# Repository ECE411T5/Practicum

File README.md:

# Practicum
Portland State University. Electrical and Computer Engineering Department. ECE 411 Practicum Project

## Team 5
* jdhobby       - Joshua Hobby
* CompileMyLife - Ibrahim Binmahfood
* Ghonimo       - Mohamed Ghonim
* DrFumador     - Mohamed Ashkanani

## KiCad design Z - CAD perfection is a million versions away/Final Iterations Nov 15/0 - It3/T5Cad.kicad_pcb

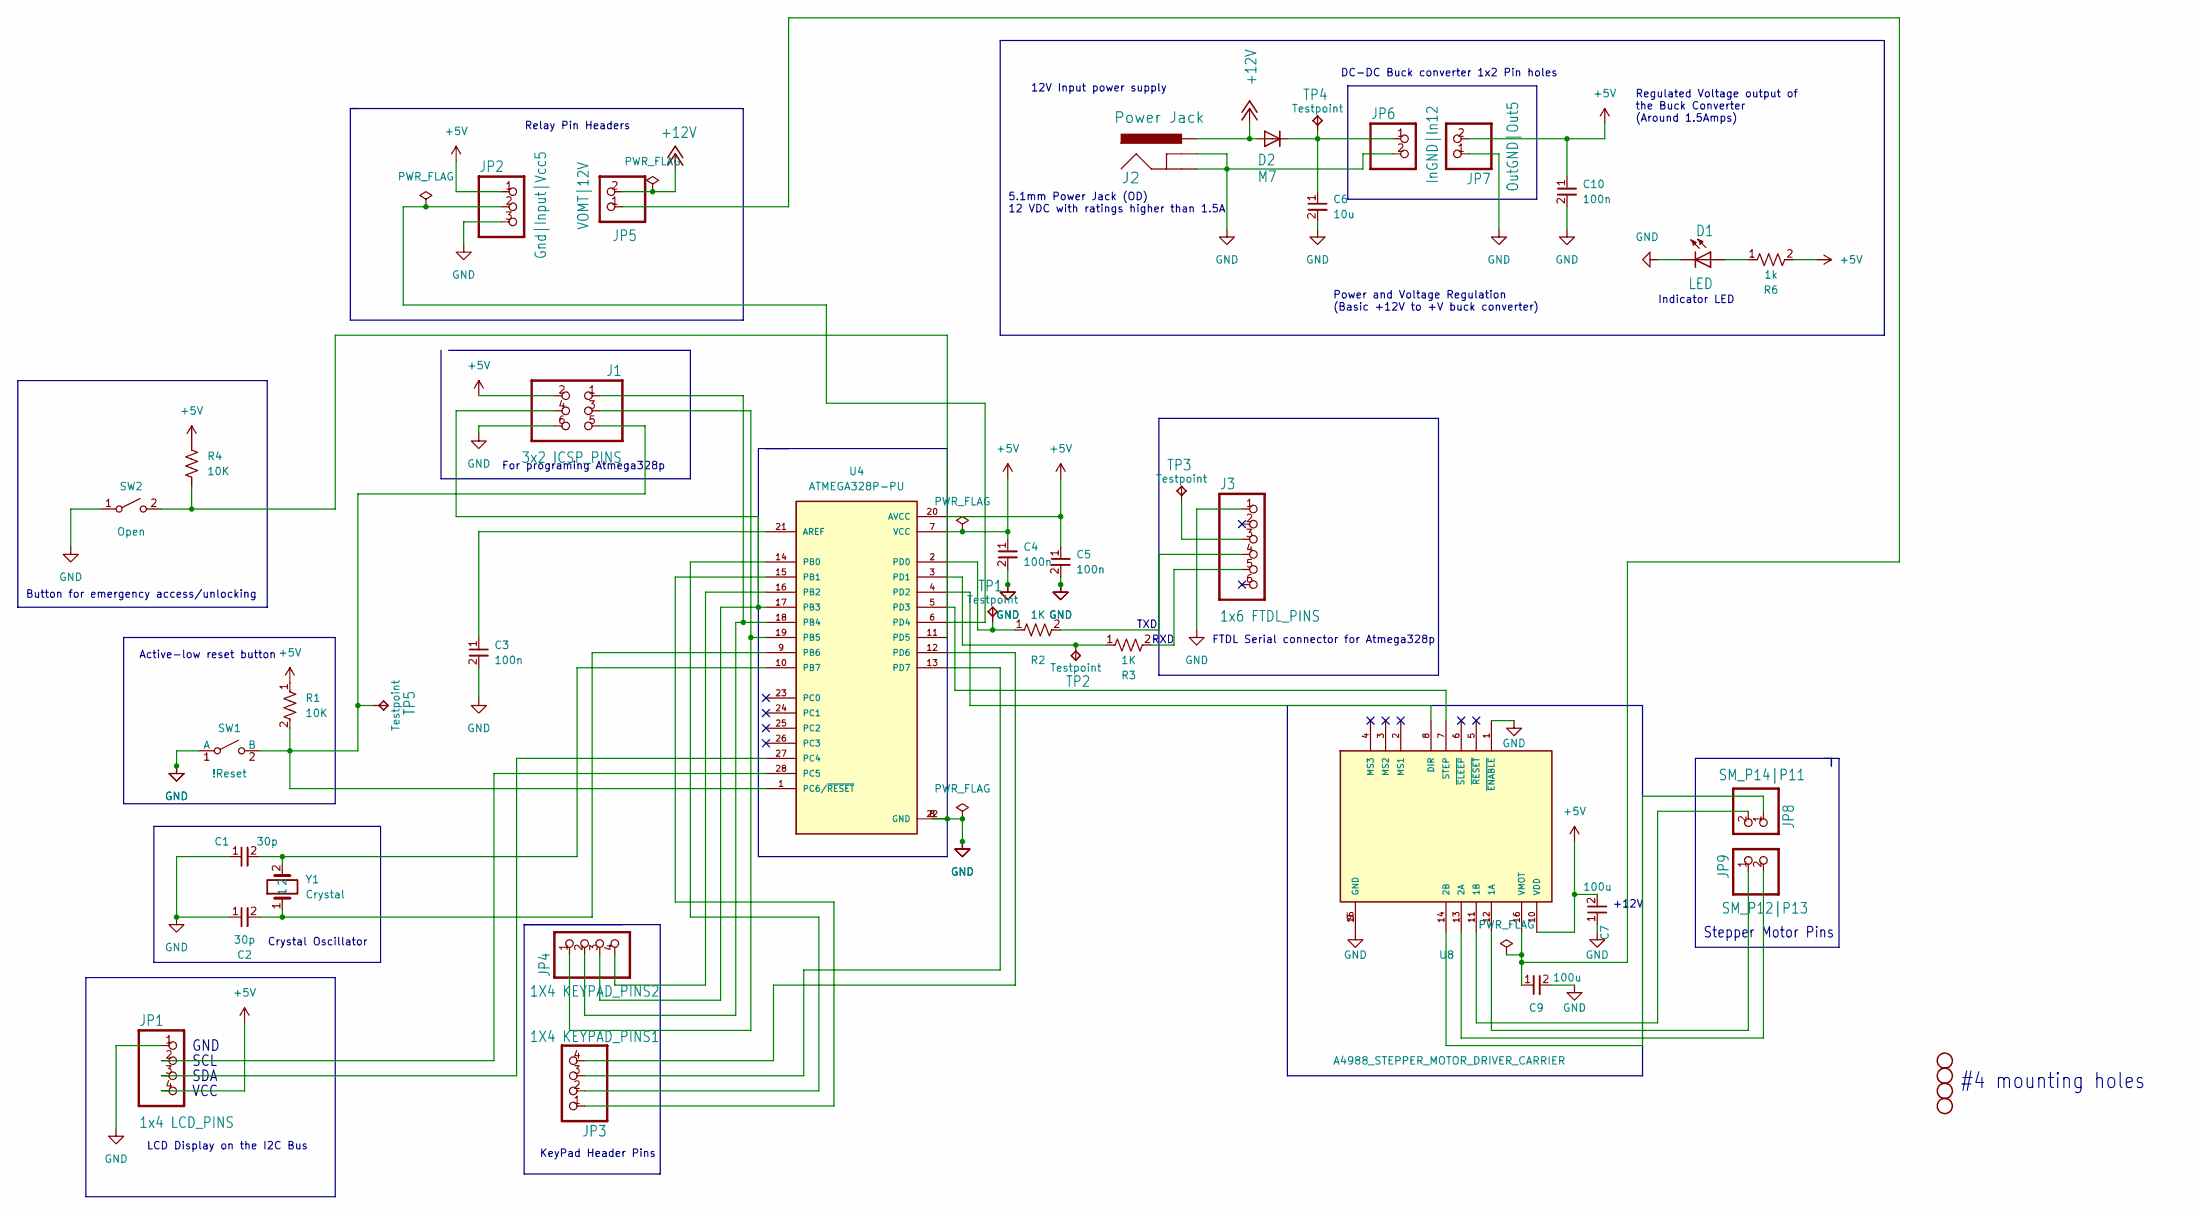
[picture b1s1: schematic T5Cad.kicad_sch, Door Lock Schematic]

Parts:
C1, C2: 30p; C0805K
C3, C4, C5, C10: 100n; C0805K
C6: 10u; C0805K
C7, C9: 100u; C0805K
D1: CHIP-LED0805
D2: SMB
H1, H2, H3, H4: STAND-OFF
J1: 2X03
J2: POWER_JACK_PTH
J3: 1X06
JP1: 1x4 LCD_PINS; 1X04
JP2: Gnd|Input|Vcc5; 1X03
JP3: 1X4 KEYPAD_PINS1; 1X04
JP4: 1X4 KEYPAD_PINS2; 1X04
JP5: VOMT|12V; 1X02
JP6: InGND|In12; 1X02
JP7: OutGND|Out5; 1X02
JP8: SM_P14|P11; 1X02
JP9: SM_P12|P13; 1X02
R1, R4: 10K; R0805
R2, R3: 1K; R0805
R6: 1k; R0805
SW1: !Reset; TACTILE_SWITCH_SMD
SW2: Open; TACTILE_SWITCH_SMD
TP1, TP2, TP3, TP4, TP5: Testpoint; P1-13
U4: ATMEGA328P-PU; DIL28-3
U8: A4988_STEPPER_MOTOR_DRIVER_CARRIER; MODULE_A4988_STEPPER_MOTOR_DRIVER_CARRIER
Y1: Crystal; HC49UP

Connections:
+5V: C4.1, C5.1, C7.2, C10.1, J1.2, JP1.4, JP2.1, JP7.2, R1.1, R4.1, R6.2, U4.7 (VCC), U4.20 (AVCC), U8.10 (VDD)
+12V: D2.A, J2.PWR, JP5.2
GND: C1.1, C2.1, C3.2, C4.2, C5.2, C6.2, C7.1, C9.2, C10.2, D1.C, J1.6, J2.GND, J2.GNDBREAK, J3.1, JP1.1, JP2.3, JP6.2, JP7.1, SW1.1 (A), SW2.1 (A), U4.8 (GND), U4.22 (GND), U8.1 (~ENABLE), U8.9 (GND), U8.15 (GND)
unnamed: C1.2, U4.10 (PB7), Y1.2
unnamed: C2.2, U4.9 (PB6), Y1.1
unnamed: C3.1, U4.21 (AREF)
unnamed: C6.1, D2.C, JP6.1, TP4.TP
unnamed: C9.1, JP5.1, U8.16 (VMOT)
unnamed: D1.A, R6.1
unnamed: J1.1, JP4.2, U4.18 (PB4)
unnamed: J1.3, JP4.1, U4.19 (PB5)
unnamed: J1.4, JP4.3, U4.17 (PB3)
unnamed: J1.5, R1.2, SW1.2 (B), TP5.TP, U4.1 (PC6/~RESET)
unnamed: J3.3, TP3.TP
unnamed: J3.4, R2.2
unnamed: J3.5, R3.2
unnamed: JP1.2, U4.28 (PC5)
unnamed: JP1.3, U4.27 (PC4)
unnamed: JP2.2, U4.6 (PD4)
unnamed: JP3.1, U4.15 (PB1)
unnamed: JP3.2, U4.14 (PB0)
unnamed: JP3.3, U4.13 (PD7)
unnamed: JP3.4, U4.12 (PD6)
unnamed: JP4.4, U4.16 (PB2)
unnamed: JP8.1, U8.14 (2B)
unnamed: JP8.2, U8.11 (1B)
unnamed: JP9.1, U8.12 (1A)
unnamed: JP9.2, U8.13 (2A)
unnamed: R2.1, TP1.TP, U4.2 (PD0)
unnamed: R3.1, TP2.TP, U4.3 (PD1)
unnamed: R4.2, SW2.2 (B), U4.11 (PD5)
unnamed: U4.4 (PD2), U8.8 (DIR)
unnamed: U4.5 (PD3), U8.7 (STEP)

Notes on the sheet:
SCL
#4 mounting holes
12V Input power supply
DC-DC Buck converter 1x2 Pin holes
KeyPad Header Pins
FTDL Serial connector for Atmega328p
Relay Pin Headers
LCD Display on the I2C Bus
RXD
Power and Voltage Regulation (Basic +12V to +V buck converter)
Button for emergency access/unlocking
Stepper Motor Pins
For programing Atmega328p
5.1mm Power Jack (OD) 12 VDC with ratings higher than 1.5A
Active-low reset button
+12V
VCC
Regulated Voltage output of the Buck Converter (Around 1.5Amps)
TXD
Indicator LED
GND
SDA
Crystal Oscillator

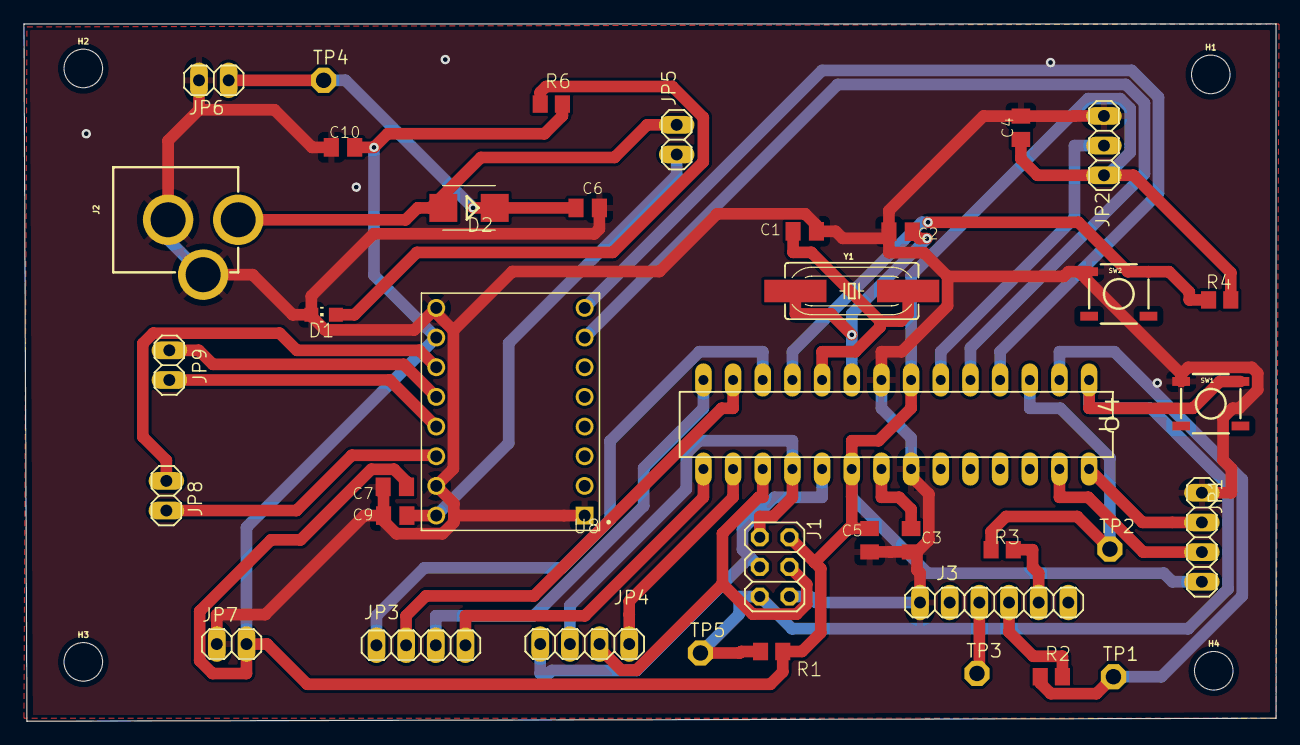
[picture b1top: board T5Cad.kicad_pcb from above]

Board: 2 copper layers, 107.2 x 59.7 mm, 42 parts (0 on the bottom side), 33 nets.

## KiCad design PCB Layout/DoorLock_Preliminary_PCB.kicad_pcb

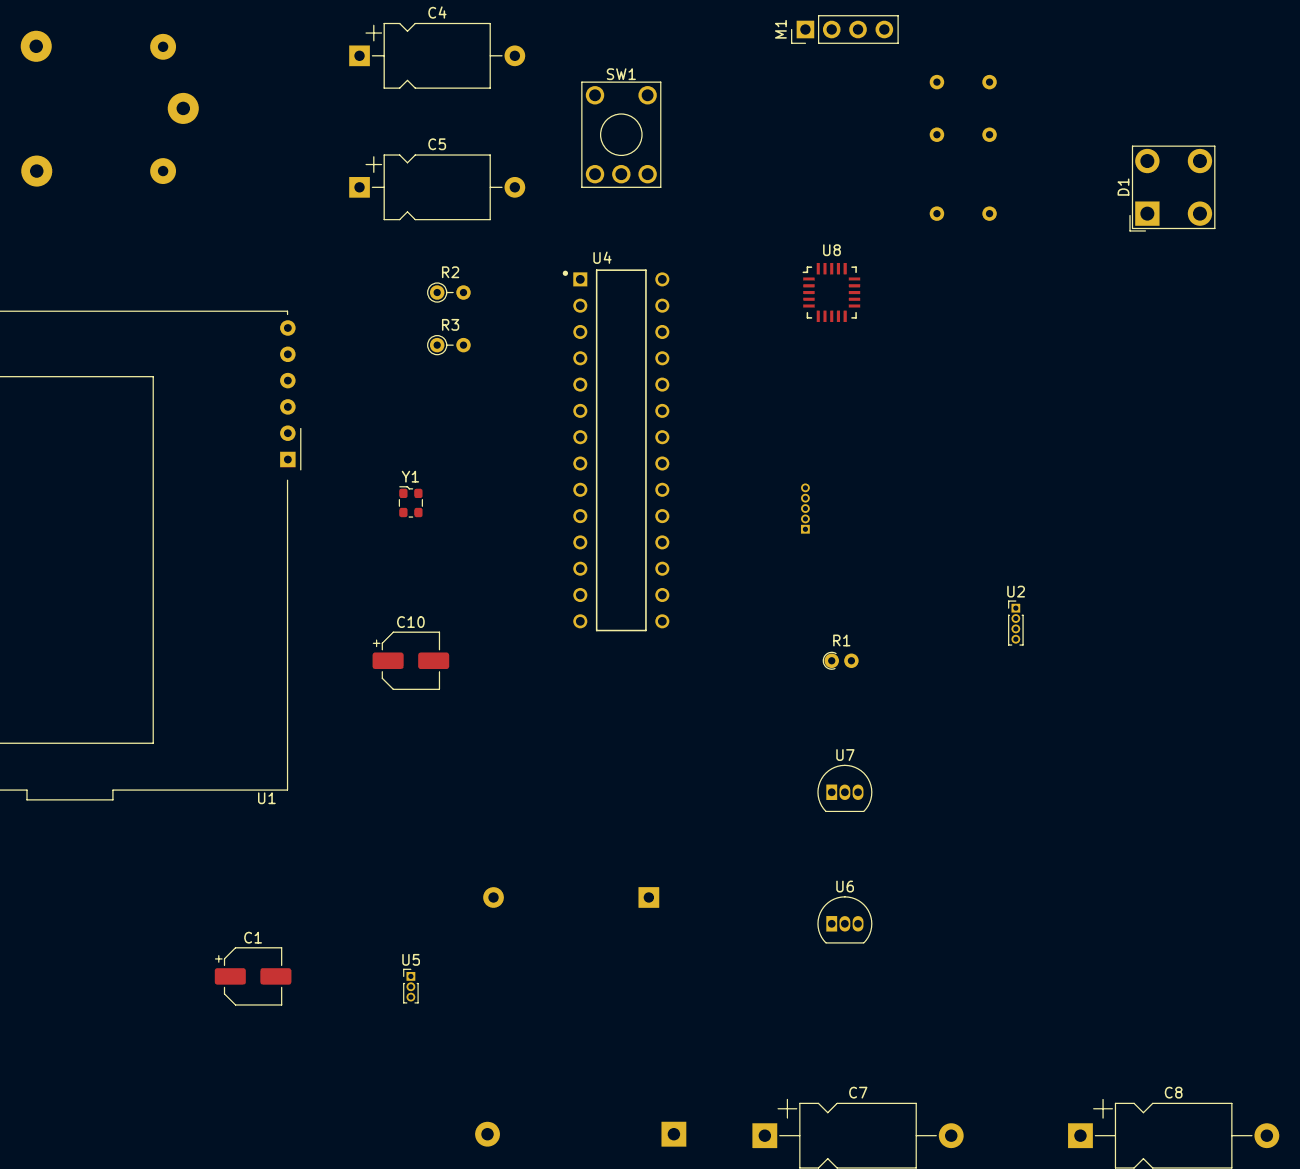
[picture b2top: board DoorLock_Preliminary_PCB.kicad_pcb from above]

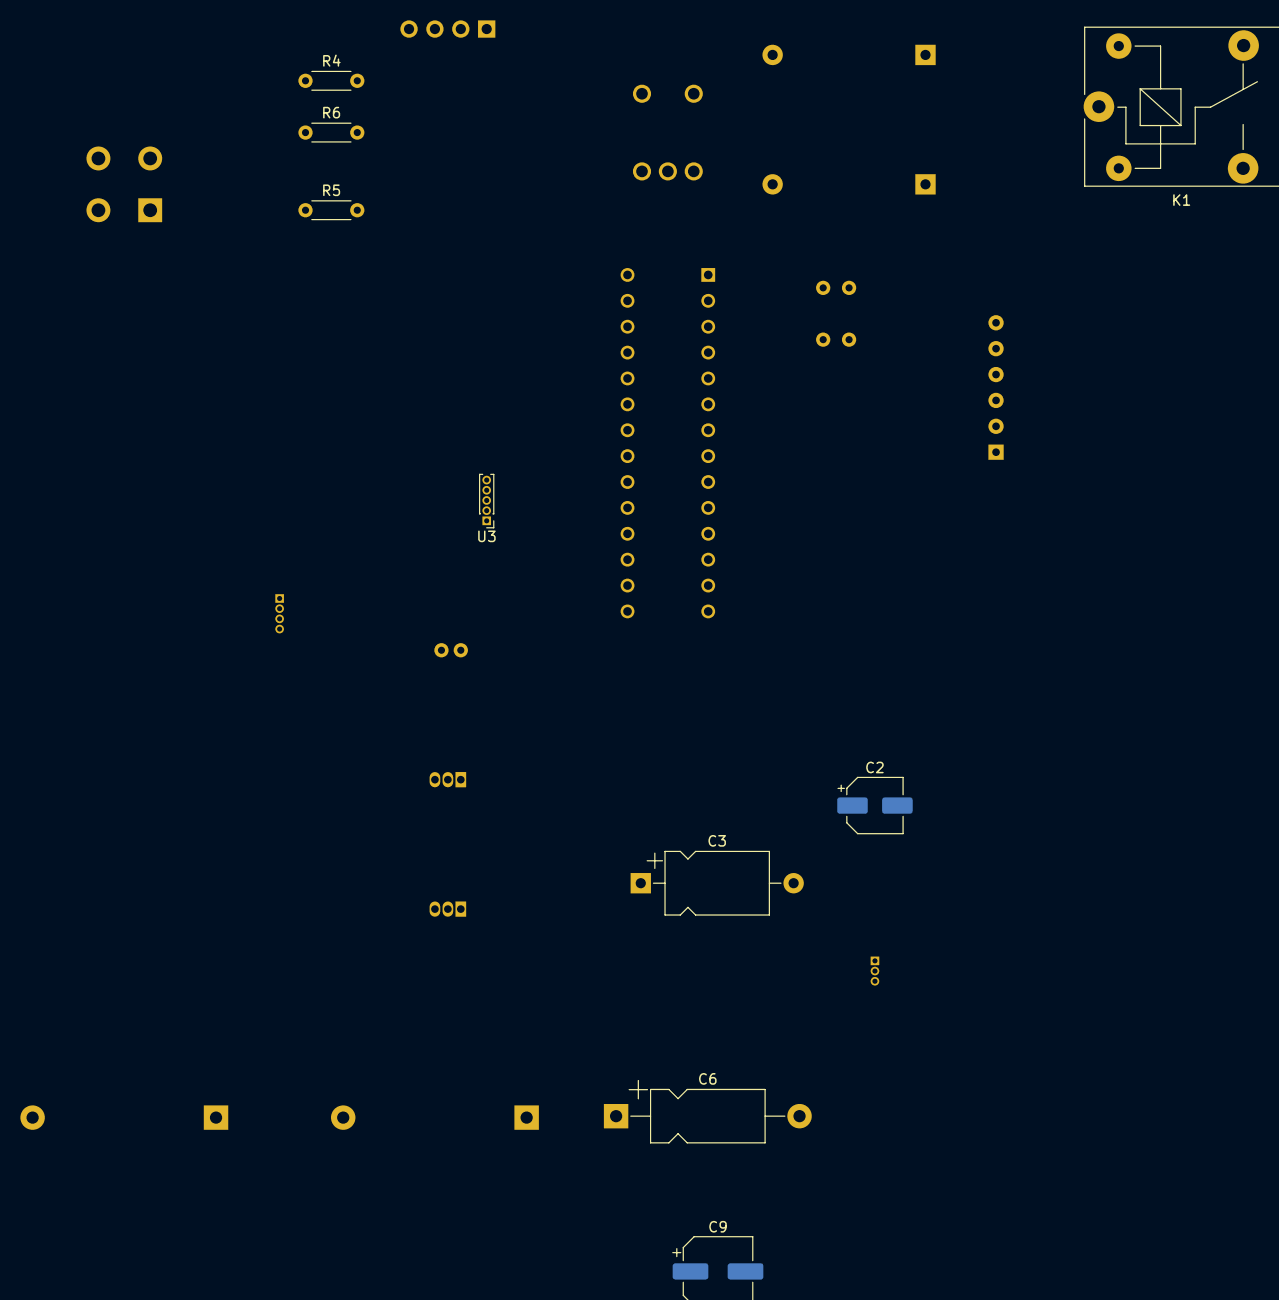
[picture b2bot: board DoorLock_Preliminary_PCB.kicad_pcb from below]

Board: 2 copper layers, 29 parts (9 on the bottom side), 25 nets, no tracks yet.

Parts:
C1, C2: 30p; CP_Elec_5x4.5
C3, C4, C5: 100n; CP_Axial_L10.0mm_D6.0mm_P15.00mm_Horizontal
C6: 220u; CP_Axial_L11.0mm_D5.0mm_P18.00mm_Horizontal
C7, C8: 0.1u; CP_Axial_L11.0mm_D6.0mm_P18.00mm_Horizontal
C9: 100n; CP_Elec_6.3x3.9
C10: 22u; CP_Elec_5x5.8
D1: LED; LED_BL-FL7680RGB
K1: SANYOU_SRD_Form_C; Relay_SPDT_SANYOU_SRD_Series_Form_C
M1: Stepper_Motor_bipolar; PinHeader_1x04_P2.54mm_Vertical
R1: 10K; R_Axial_DIN0204_L3.6mm_D1.6mm_P1.90mm_Vertical
R2, R3: 1K; R_Axial_DIN0204_L3.6mm_D1.6mm_P2.54mm_Vertical
R4, R5, R6: 0.5; R_Axial_DIN0204_L3.6mm_D1.6mm_P5.08mm_Horizontal
SW1: Reset; KSA_Tactile_SPST
U1: EA_T123X-I2C
U2: Keypad; PinHeader_1x04_P1.00mm_Vertical
U3: ICSP; PinHeader_1x05_P1.00mm_Vertical
U4: ATMEGA328P-PU; DIP794W46P254L2967H457Q28B
U5: FTDI_TTL; PinHeader_1x03_P1.00mm_Vertical
U6, U7: L7805; TO-92_Inline
U8: A4988_STEPPER_MOTOR_DRIVER_CARRIER; AMS_LGA-20_4.7x4.5mm_P0.65mm
Y1: Crystal; Oscillator_SMD_ECS_2520MV-xxx-xx-4Pin_2.5x2.0mm

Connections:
+5V: C4.1, C5.1, C8.1, C10.1, K1.1, K1.2, R1.1, R4.2, R5.2, R6.2, U1.2 (VDD), U3.2, U4.7 (VCC), U4.20 (AVCC), U8.10 (VDD)
GND: C1.1, C2.1, C3.2, C4.2, C5.2, C6.2, C7.2, C8.2, C9.2, C10.2, D1.1 (K), K1.3, K1.4, SW1.1 (A), U1.1 (VSS), U4.8 (GND), U4.22 (GND), U5.1, U6.2 (GND), U7.2 (GND), U8.9 (GND), U8.15 (GND)
unnamed: C1.2, U4.10 (PB7), Y1.2
unnamed: C2.2, U4.9 (PB6), Y1.1
unnamed: C3.1, U4.21 (AREF)
unnamed: D1.2 (A), R6.1
unnamed: K1.5, U4.6 (PD4)
unnamed: M1.1, U8.12 (1A)
unnamed: M1.2 (-), U8.11 (1B)
unnamed: M1.3, U8.13 (2A)
unnamed: M1.4, U8.14 (2B)
unnamed: R1.2, SW1.2 (B), U3.5, U4.1 (PC6/~RESET)
unnamed: R2.1, U4.2 (PD0)
unnamed: R3.1, U4.3 (PD1)
unnamed: R4.1, U6.3 (OUT)
unnamed: R5.1, U7.3 (OUT)
unnamed: U1.5 (SDA), U4.28 (PC5)
unnamed: U1.6 (SCL), U4.27 (PC4)
unnamed: U2.1, U3.3, U4.19 (PB5)
unnamed: U2.2, U3.1, U4.18 (PB4)
unnamed: U2.3, U3.4, U4.17 (PB3)
unnamed: U2.4, U4.16 (PB2)
unnamed: U4.4 (PD2), U8.8 (DIR)
unnamed: U4.5 (PD3), U8.7 (STEP)
VDD: C6.1, C7.1, C9.1, U6.1 (IN), U7.1 (IN), U8.16 (VMOT)

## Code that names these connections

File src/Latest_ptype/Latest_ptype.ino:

/* Team 5:  Mohamed Ghonim
 *          Joshua Hobby
 *          Mohamed Ashkanani
 *          Ibrahim Binmahfood
 * 
 * Inspiration:
 * https://github.com/camdeno/ECE-411-Team-5
 * 
 * NOTE: status_btn which is output from UNLOCK_BTN pin on PCB is 
 * supposed to be a pull down resistor rather than pull up.
 */
 
#include <LiquidCrystal_I2C.h> // Frank de Brabander's LiquidCrystal_I2C v1.1.2
#include <Keypad.h>

#define STEPS_PER_REV 200
#define STEPS_REQ     65
#define M_SPEED       2000

// Connected to PD2 and PD3
#define DIR           2
#define STEP          3

// Connected to PD4
#define RELAY_SIG     4

// Connected to PD5
#define UNLOCK_BTN    5

// 4x4 Keypad w/ 4 rows and 4 cols
#define ROW           4
#define COL           4

// LCD Configuration
#define LCD_ROW 2
#define LCD_COL 16

// LCD I2C Address: 0x27 from datasheet
#define LCD_I2C_ADD 0x27
  
// The formatting of 4x4 Keypad
char keymap[ROW][COL] = {
  {'1', '2', '3', 'A'},
  {'4', '5', '6', 'B'},
  {'7', '8', '9', 'C'},
  {'*', '0', '#', 'D'}
};

// Pins D[6:9] from PD[6:7] and PB[0:1]
// Pins D[10:13] from PB[2:5]
byte pin_R[ROW] = {6, 7, 8, 9};
byte pin_C[COL] = {10, 11, 12, 13};

String valid_key = "12312";
char clr_key = 'C';
String entered_key = "00000";
int num_keys = 0;
int l_flag = 0; // UNLOCKED(0), LOCKED(1)

// Set to 0 initially
int status_btn = 0;

// Global Object Declarations
Keypad keypad = Keypad(makeKeymap(keymap), pin_R, pin_C, ROW, COL);
LiquidCrystal_I2C lcd(LCD_I2C_ADD, LCD_COL, LCD_ROW);

void setup(){
    
    Serial.begin(9600);
    Serial.println("Initializing...");

    // Relay Position and set to be OUTPUT
    pinMode(RELAY_SIG, OUTPUT);
    relay_pos(0);   // Set signal to LO

    // Emergency Unlock button set to INPUT
    pinMode(UNLOCK_BTN, INPUT);

    // Stepper Motor Driver STEP and DIR as OUTPUTs
    pinMode(STEP, OUTPUT);
    pinMode(DIR, OUTPUT);
    
    // LCD Initialization
    lcd.init();
    lcd.backlight();
    lcd.begin(LCD_COL, LCD_ROW);
   
    scrWrite("Enter Key       ","_____         ");
    Serial.println("Enter Key");
}
void loop(){
  //Recieve the key pressed
  char key_r = keypad.getKey();
  
  if (key_r){
      relay_pos(1);     // Set signal to HI
      entered_key[num_keys] = key_r;   // store key recieved to array
      num_keys = num_keys + 1;        // increment number of keys (idx)
      Serial.println("Digit Recieved:");
      Serial.println(key_r);
  
      writeCode(num_keys - 1, key_r);
  
      // check if entered key is same as valid key
      if (entered_key == valid_key){
          num_keys = 0;
          entered_key = "00000";
  
          // Check if Unlocked (0)
          if (l_flag == 0){
              Serial.println("Entered Key... Valid! Locking Door...");
              scrWrite("Key is...Valid!", "Locking Door...");
              stepTurn(STEPS_REQ, 1, M_SPEED);
              scrWrite("       Door    ", "    Locked!    ");
              l_flag = 1; // Locked
              delay(2000);
              relay_pos(0);   // Set signal to LO
              scrWrite("Enter Key      ", "_____          ");
          }
  
          // Check if Locked (1)
          else if (l_flag == 1){
              Serial.println("Entered Key... Valid. Unlocking Door...");
              scrWrite("Key is...Valid!", "Unlocking Door...");
              stepTurn(STEPS_REQ, 0, M_SPEED);
              Serial.println("Door Unlocked.   ");
              scrWrite("     Door     ", "   Unlocked!   ");
              l_flag = 0;
              delay(2000);
              relay_pos(0);   // Set signal to LO
              scrWrite("Enter Key     ", "_____          ");
          }
      }
  
      // Check if key recieved is the Clear key 'C'
      else if (key_r == clr_key){
          Serial.println("Key cleared!");
          scrWrite("     Key    ","    Cleared    ");
          delay(2000);
          relay_pos(0);     // Set signal to LO
          scrWrite("Enter Key      ", "_____          ");
          entered_key = "00000";
          num_keys = 0;
      }
  
      // Check if number of keys recieved is greater than 5 LIMIT
      else if(num_keys >= 5){
          entered_key = "00000";
          num_keys = 0;
          Serial.println("Invalid Key. Try again...");
          scrWrite("Incorrect Key! ","Try again...");
          delay(2000);
          relay_pos(0);     // Set signal to LO
          scrWrite("Enter Key      ", "_____          ");
      }
  }
  
  // Read the UNLOCK_BTN was toggled and get returned value
  status_btn = digitalRead(UNLOCK_BTN);
  Serial.println("Status Button:");
  Serial.println(status_btn);
  
  // Check if both status returned is 1 AND the num of keys is set 0
  // NOTE: status_btn which is output from UNLOCK_BTN pin on PCB is 
  // supposed to be a pull down resistor rather than pull up. So it is
  // negated with '!'.
  if ((!(status_btn) == 1) && (num_keys == 0)){
  
    // Check if the lock flag is 0
    if (l_flag == 0){
      scrWrite("   Locking...  ", "     Door     ");
      relay_pos(1); // Set the signal HI
      delay(2000);
      stepTurn(STEPS_REQ, 1, M_SPEED);
      delay(2000);
      relay_pos(0); // Set the signal LO
      scrWrite("Enter Key     ", "_____          ");
      l_flag = 1;
      num_keys = 0;
    }
  
    // Check if the lock flag is 1
    else if (l_flag == 1){
      scrWrite(" Unlocking...  ", "    Door    ");
      relay_pos(1);  // Set the signal HI
      delay(2000);
      stepTurn(STEPS_REQ, 0, M_SPEED);
      delay(2000);
      relay_pos(0);  // Set the signal LO
      scrWrite("Enter Key      ", "_____          ");
      l_flag = 0;
      num_keys = 0;
    }
  }
}


void scrWrite(char upperWord[16], char lowerWord[16])
{
  lcd.backlight();
  lcd.setCursor(0, 0);
  lcd.print(upperWord);
  lcd.setCursor(0, 1);
  lcd.print(lowerWord);
}

void writeCode(int cursor_pos, char key)
{
  lcd.backlight();
  lcd.setCursor(cursor_pos, 1);
  lcd.print(key);
}

void relay_pos(int state){
  if (state == 1){
    digitalWrite(RELAY_SIG, HIGH);
  }
  else if (state == 0){
    digitalWrite(RELAY_SIG, LOW);
  }
}

void stepTurn(int rev, int dir, int speed_m)
{
  digitalWrite(DIR, dir); // 1 for CW and 0 for CCW

  for (int x = 0; x < rev; x++)
  {
    digitalWrite(STEP, HIGH);
    delayMicroseconds(speed_m); // Increase delay for slower rotation
    digitalWrite(STEP, LOW);
    delayMicroseconds(speed_m);
  }
}







    

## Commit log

2022-11-10 Rough Draft of Functional Decomposition
2022-11-10 Final Draft
2022-11-14 Initial Prototype code and outline/buildsystem
2022-11-20 removed the targets and variables for the minipro programmer since it stopped working
2022-11-20 Using Arduino to prototype
2022-12-01 functioning code but keypad ordering is reversed (cols to rows)
2022-12-01 The initial protoype using the 1602A LCD Display without I2C and figuring things out
2022-12-03 Working Relay code, and RESET/UNLOCK button codes configured. Although, keymap formatting is still buggy and reversed
2022-12-08 latest stable code on breadboard prototype
2022-12-08 added inspiration source
